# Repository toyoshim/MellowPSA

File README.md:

# MellowPSA

I/O 1981年6月号に掲載されたPSAを元にして以下の修正を行ったもの

- 入手困難になりつつあるロジックICはまとめてCPLD（MAX7000）で実装した
- RAM制御信号のワンショット化の回路はコンデンサの充電を利用した回路から、同期回路に変更した
- MOVE転送を実行する際、RAM制御だけでなくキャラクターデータ出力もワンショット化した
- 3声化対応のため、I/O 02Hのb6とb7をラッチし、それぞれGATE 1、GATE 2に接続した
- 3声とBEEP音のミックス・増幅回路はM.K WorkshopさんのPSA基板を参考に実装した
- 128キャラクターモートに加え、256キャラクターモードを追加実装した
- OFF、128キャラクターモード、256キャラクターモードはリセットボタンでローテーションで切り替わるように実装した（記事に載っていたリセットボタンでON/OFFにする方法を参考にしている）
- 電源投入時の動作モードを確実にOFFモードに設定するため、電源投入後しばらくLOWに張り付くPON信号をコンデンサのチャージを利用して導入した

注意点
- 現時点でコミットされている基板データはキャラROMの実装位置が2.5ピン分左に寄っているので、新規に作る際には修正してボードを作るべし
- 基板データで用いているSRAMが既に入手困難かもしれない
- そもそもCPLDのMAX7000が入手困難

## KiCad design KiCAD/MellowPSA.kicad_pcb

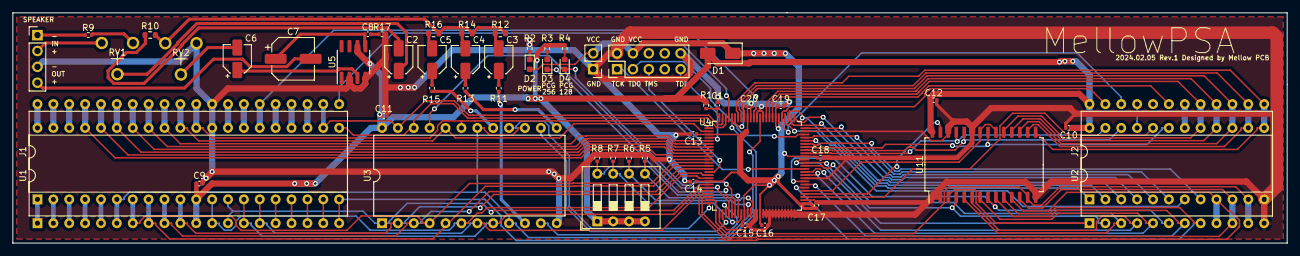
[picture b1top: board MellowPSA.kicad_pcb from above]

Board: 2 copper layers, 203.8 x 36.8 mm, 55 parts (0 on the bottom side), 115 nets.

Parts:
C1: 3.3u; C_0402_1005Metric
C2, C3, C4, C5, C6: 10u; CP_Elec_4x5.4
C7: 220u; CP_Elec_6.3x5.4
C8: 0.047u; C_0402_1005Metric
C9, C10, C11, C12, C13, C14, C15, C16, C17, C18, C19, C20: 0.1u; C_0402_1005Metric
D1: D; D_SMA
D2: LED_PWR; LED_0603_1608Metric
D3: LED_256; LED_0603_1608Metric
D4: LED_ON; LED_0603_1608Metric
J1: Z80Socket; DIP-40_W15.24mm
J2: D2716Sock; DIP-24_W15.24mm
J3: JTAG; PinHeader_2x05_P2.54mm_Vertical
J4: PWR; PinHeader_1x02_P2.54mm_Vertical
J5: SP; PinHeader_1x04_P2.54mm_Vertical
R1, R5, R6, R7, R8: 10k; R_0402_1005Metric
R2, R3, R4: 1k; R_0402_1005Metric
R9, R11, R13, R15: 2K; R_0402_1005Metric
R10, R12, R14, R16: 5.6K; R_0603_1608Metric
R17: 10; R_0402_1005Metric
RV1, RV2: 1K; RV-RM-065
SW1: SW_DIP_x04; SW_DIP_SPSTx04_Slide_9.78x12.34mm_W7.62mm_P2.54mm
U1: Z80CPU; DIP-40_W15.24mm
U2: D2716; DIP-24_W15.24mm
U3: 8253; DIP-24_W15.24mm
U4: EPM7128S100(TQFP); TQFP-100_14x14mm_P0.5mm
U5: LM386; SOP-8_3.76x4.96mm_P1.27mm
U11: SRM2B256SLMX; SOIC-28W_8.4x18.7mm_P1.27mm_SRM2B256

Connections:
/A0: J1.30 (A0), U1.30 (A0), U3.19 (A0), U4.1 (I/O)
/A1: J1.31 (A1), U1.31 (A1), U3.20 (A1), U4.2 (I/O)
/A2: J1.32 (A2), U1.32 (A2), U4.5 (I/O)
/A3: J1.33 (A3), U1.33 (A3), U4.6 (I/O)
/A4: J1.34 (A4), U1.34 (A4), U4.7 (I/O)
/A5: J1.35 (A5), U1.35 (A5), U4.8 (I/O)
/A6: J1.36 (A6), U1.36 (A6), U4.9 (I/O)
/A7: J1.37 (A7), U1.37 (A7), U4.10 (I/O)
/A8: J1.38 (A8), U1.38 (A8)
/A9: J1.39 (A9), U1.39 (A9)
/A10: J1.40 (A10), U1.40 (A10)
/A11: J1.1 (A11), U1.1 (A11)
/A12: J1.2 (A12), U1.2 (A12)
/A13: J1.3 (A13), U1.3 (A13)
/A14: J1.4 (A14), U1.4 (A14)
/A15: J1.5 (A15), U1.5 (A15)
/CA0: U2.8, U4.56 (I/O), U11.10 (A0)
/CA1: U2.7, U4.57 (I/O), U11.9 (A1)
/CA2: U2.6, U4.58 (I/O), U11.8 (A2)
/CA3: U2.5, U4.60 (I/O), U11.7 (A3)
/CA4: U2.4, U4.61 (I/O), U11.6 (A4)
/CA5: U2.3, U4.63 (I/O), U11.5 (A5)
/CA6: U2.2, U4.64 (I/O), U11.4 (A6)
/CA7: U2.1, U4.65 (I/O), U11.3 (A7)
/CA8: U2.23, U4.67 (I/O), U11.25 (A8)
/CA9: U2.22, U4.68 (I/O), U11.24 (A9)
/CA10: U2.19, U4.69 (I/O), U11.21 (A10)
/CCS2: J2.18, U2.18
/CCS3: J2.21, U2.21
/CD0: J2.9, U2.9, U4.22 (I/O), U11.11 (D0)
/CD1: J2.10, U2.10, U4.23 (I/O), U11.12 (D1)
/CD2: J2.11, U2.11, U4.24 (I/O), U11.13 (D2)
/CD3: J2.13, U2.13, U4.94 (I/O), U11.15 (D3)
/CD4: J2.14, U2.14, U4.93 (I/O), U11.16 (D4)
/CD5: J2.15, U2.15, U4.92 (I/O), U11.17 (D5)
/CD6: J2.16, U2.16, U4.85 (I/O), U11.18 (D6)
/CD7: J2.17, U2.17, U4.84 (I/O), U11.19 (D7)
/D0: J1.14 (D0), U1.14 (D0), U3.8 (D0), U4.20 (I/O)
/D1: J1.15 (D1), U1.15 (D1), U3.7 (D1), U4.21 (I/O)
/D2: J1.12 (D2), U1.12 (D2), U3.6 (D2), U4.17 (I/O)
/D3: J1.8 (D3), U1.8 (D3), U3.5 (D3), U4.13 (I/O)
/D4: J1.7 (D4), U1.7 (D4), U3.4 (D4), U4.12 (I/O)
/D5: J1.9 (D5), U1.9 (D5), U3.3 (D5), U4.14 (I/O)
/D6: J1.10 (D6), U1.10 (D6), U3.2 (D6), U4.16 (I/O)
/D7: J1.13 (D7), U1.13 (D7), U3.1 (D7), U4.19 (I/O)
/DIPSW0: R5.1, SW1.5, U4.36 (I/O)
/DIPSW1: R6.1, SW1.6, U4.35 (I/O)
/DIPSW2: R7.1, SW1.7, U4.33 (I/O)
/DIPSW3: R8.1, SW1.8, U4.32 (I/O)
/FA0: J2.8, U4.70 (I/O)
/FA1: J2.7, U4.71 (I/O)
/FA2: J2.6, U4.72 (I/O)
/FA3: J2.5, U4.75 (I/O)
/FA4: J2.4, U4.76 (I/O)
/FA5: J2.3, U4.77 (I/O)
/FA6: J2.2, U4.78 (I/O)
/FA7: J2.1, U4.79 (I/O)
/FA8: J2.23, U4.80 (I/O)
/FA9: J2.22, U4.81 (I/O)
/FA10: J2.19, U4.83 (I/O)
/IN+: J5.2, RV1.3
/IN-: J5.1, R9.1
/LED0: D4.1 (K), U4.31 (I/O)
/LED1: D3.1 (K), U4.30 (I/O)
/OUT+: C7.2, J5.4
/PON: C1.2, R1.2, U4.100 (I/O)
/TCK: J3.1, U4.62 (I/O/TCK)
/TDI: J3.9, U4.4 (I/O/TDI)
/TDO: J3.3, U4.73 (I/O/TDO)
/TG0: U3.11 (G0), U4.28 (I/O)
/TG1: U3.14 (G1), U4.27 (I/O)
/TG2: U3.16 (G2), U4.25 (I/O)
/TMS: J3.5, U4.15 (I/O/TMS)
/TO0: R11.1, U3.10 (OUT0)
/TO1: R13.1, U3.13 (OUT1)
/TO2: R15.1, U3.17 (OUT2)
/V_CPLD: C13.1, C14.1, C15.1, C16.1, C17.1, C18.1, C19.1, C20.1, D1.1 (K), D2.2 (A), J3.4, J4.2, U4.3 (VCCIO), U4.18 (VCCIO), U4.34 (VCCIO), U4.39 (VCCINT), U4.51 (VCCIO), U4.66 (VCCIO), U4.82 (VCCIO), U4.91 (VCCINT)
//BUSACK: J1.23 (~BUSACK), U1.23 (~BUSACK)
//BUSRQ: J1.25 (~BUSRQ), U1.25 (~BUSRQ)
//CLK: J1.6 (~CLK), U1.6 (~CLK), U3.9 (CLK0), U3.15 (CLK1), U3.18 (CLK2), U4.87 (INPUT/GCLK1)
//HALT: J1.18 (~HALT), U1.18 (~HALT)
//INT: J1.16 (~INT), U1.16 (~INT)
//IORQ: J1.20 (~IORQ), U1.20 (~IORQ), U4.96 (I/O)
//M1: J1.27 (~M1), U1.27 (~M1)
//MREQ: J1.19 (~MREQ), U1.19 (~MREQ)
//NMI: J1.17 (~NMI), U1.17 (~NMI)
//RAMCS: U4.55 (I/O), U11.20 (~CS), U11.22 (~OE)
//RAMWR: U4.54 (I/O), U11.27 (~WE)
//RD: U1.21 (~RD), U3.22 (~RD), U4.98 (I/O)
//RD_MB: J1.21 (~RD), U4.97 (I/O)
//RESET: J1.26 (~RESET), U1.26 (~RESET), U4.89 (INPUT/GCLRn)
//RFSH: J1.28 (~RFSH), U1.28 (~RFSH)
//ROMCS: U2.20, U4.53 (I/O)
//TCS: U3.21 (~CS), U4.29 (I/O)
//WAIT: J1.24 (~WAIT), U1.24 (~WAIT)
//WR: J1.22 (~WR), U1.22 (~WR), U3.23 (~WR), U4.99 (I/O)
GND: C1.1, C9.2, C10.2, C11.2, C12.2, C13.2, C14.2, C15.2, C16.2, C17.2, C18.2, C19.2, C20.2, J1.29 (GND), J2.12, J3.2, J3.10, J4.1, J5.3, R2.1, R5.2, R6.2, R7.2, R8.2, R17.2, RV2.1, U1.29 (GND), U2.12, U3.12 (GND), U4.11 (GNDIO), U4.26 (GNDIO), U4.37 (I/O), U4.38 (GNDINT), U4.40 (I/O), U4.41 (I/O), U4.42 (I/O), U4.43 (GNDIO), U4.44 (I/O), U4.45 (I/O), U4.46 (I/O), U4.47 (I/O), U4.48 (I/O), U4.49 (I/O), U4.50 (I/O), U4.52 (I/O), U4.59 (GNDIO), U4.74 (GNDIO), U4.86 (GNDINT), U4.88 (INPUT/OE1), U4.90 (INPUT/OE2/GCLK2), U4.95 (GNDIO), U5.2 (-), U5.4 (GND), U11.1 (A14), U11.2 (A12), U11.14 (GND), U11.23 (A11), U11.26 (A13)
unnamed: C2.1, RV1.2
unnamed: C2.2, R10.1
unnamed: C3.1, R11.2
unnamed: C3.2, R12.1
unnamed: C4.1, R13.2
unnamed: C4.2, R14.1
unnamed: C5.1, R15.2
unnamed: C5.2, R16.1
unnamed: C6.2, RV2.2
unnamed: C7.1, C8.1, U5.5
unnamed: C8.2, R17.1
unnamed: D2.1 (K), R2.2
unnamed: D3.2 (A), R3.2
unnamed: D4.2 (A), R4.2
unnamed: R9.2, RV1.1
unnamed: R10.2, R12.2, R14.2, R16.2, RV2.3
unnamed: C6.1, U5.3 (+)
VCC: C9.1, C10.1, C11.1, C12.1, D1.2 (A), J1.11 (VCC), J2.24, R1.1, R3.1, R4.1, SW1.1, SW1.2, SW1.3, SW1.4, U1.11 (VCC), U2.24, U3.24 (VCC), U5.6 (V+), U11.28 (VCC)

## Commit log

2024-03-20 move KiCAD projects into KiCAD directory
2024-03-20 remove unnecessary files
2024-03-20 Add Quartus II project
2024-03-20 README.md
2024-03-20 Add The 3-Clause BSD License
